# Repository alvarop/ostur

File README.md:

# Ostur - Cheese cave controller!

This is a work in progress for a cheese cave controller system.
The goal is to be able to control a mini fridge to get the right conditions for cheesemaking.

The project consists of:

* [Hardware](hw/) - A microcontroller and various temperature/humidity sensors
* [Firmware](fw/2.0/) - Code in the microcontroller to control the fridge and measure temperature/humidity values
* [Software](sw/2.0/) - Python scripts to communicate with the microcontroller to log and plot data

So far, it's been used to [make Brie](https://imgur.com/a/cGHID) [successfully](https://imgur.com/B5qB1kU)!

Once it's more user friendly, I'll add usage instructions so others can reproduce the setup.

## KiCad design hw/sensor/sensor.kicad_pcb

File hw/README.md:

# Ostur Hardware

To make some brie, there are 3 main components required:
1. An [Ostur controller](controller/) PCB
2. A controllable power outlet relay module. I'm using [this one](https://www.adafruit.com/product/2935) from Adafruit
3. 2+ [Ostur temperature/humidity sensors](humidity/). One for the fridge temperature and the rest for each aging container (if any).

Optional components are:
1. [Silicon Labs BLED112](https://www.digikey.com/products/en?keywords=1446-1030-ND) USB dongle for receiving BLE beacon data of the temperature/humidity.

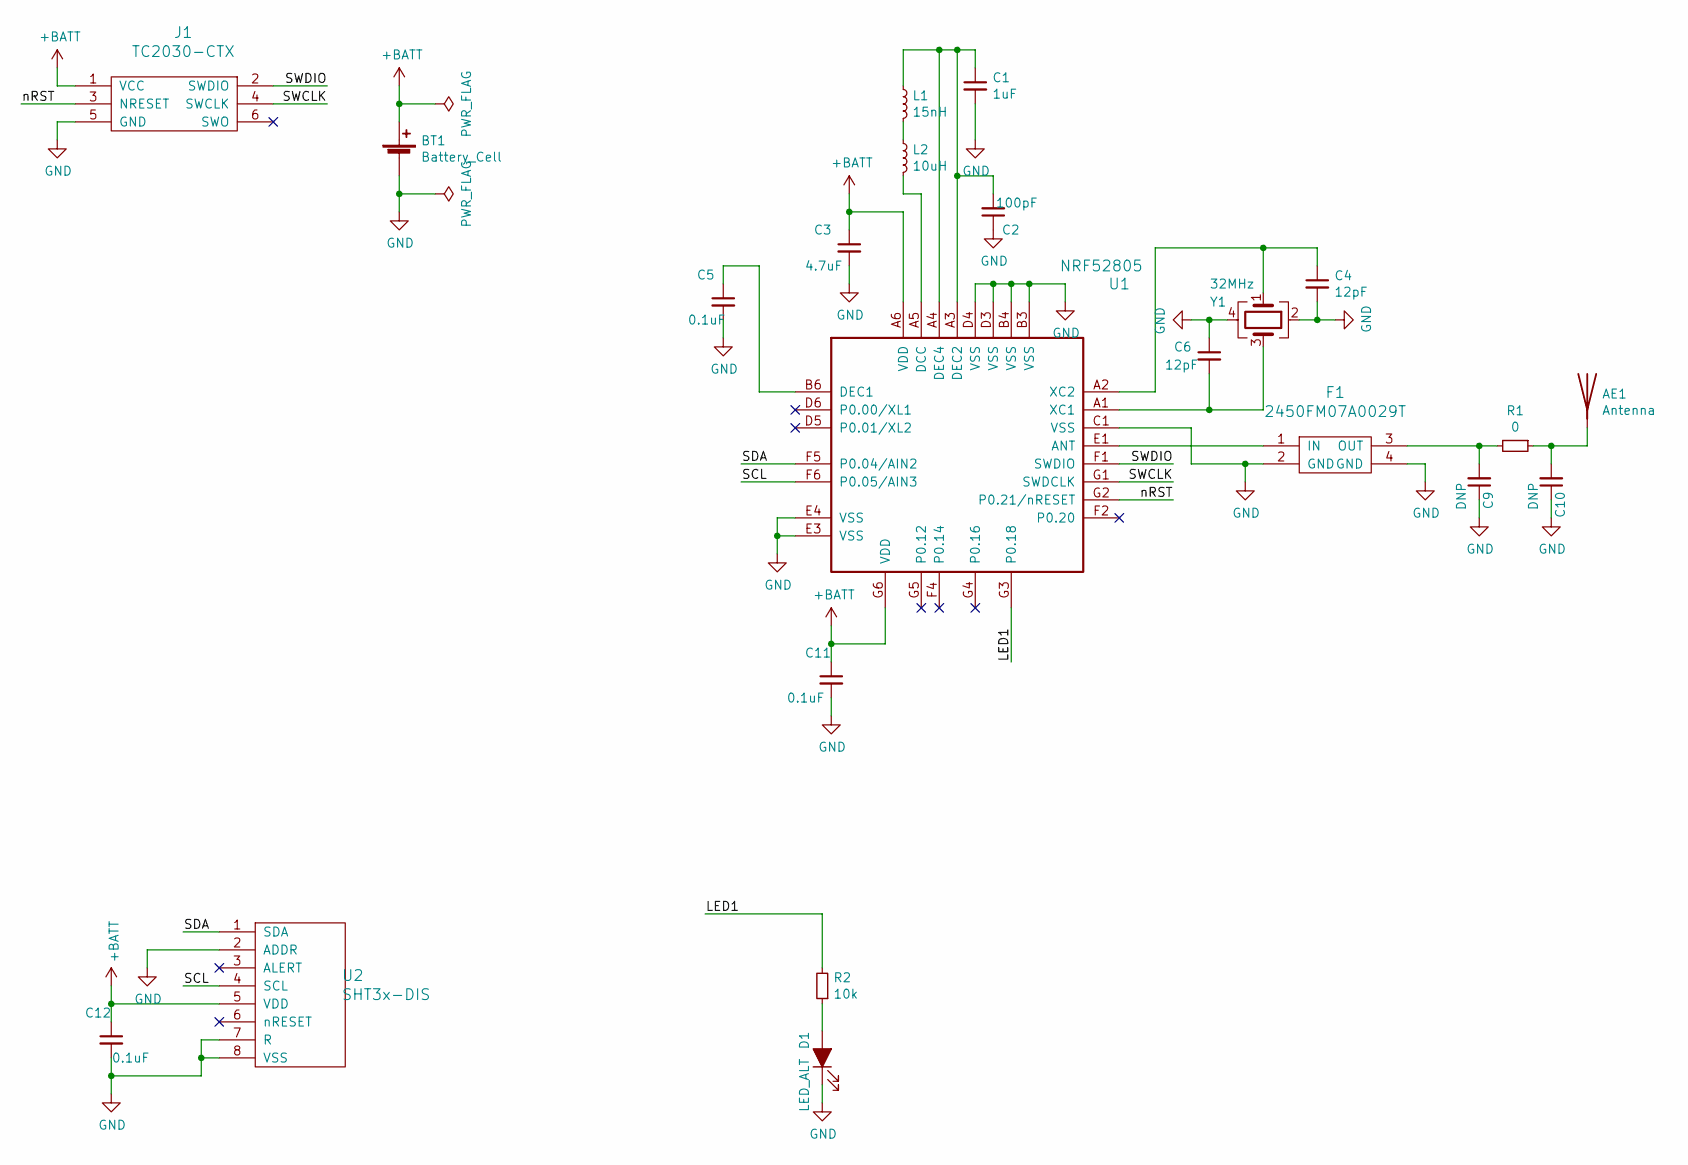
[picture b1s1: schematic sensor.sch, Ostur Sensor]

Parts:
AE1: Antenna; AMCA31-2R450G-S1F-T3; MPN AMCA31-2R450G-S1F-T3
BT1: Battery_Cell; BAT-HLD-001-THM; MPN BATT-HLD-001-THM
C1: 1uF; C_0402_1005Metric; MPN CC0402KRX5R5BB105
C2: 100pF; C_0402_1005Metric; MPN UMK105CG101JV-F
C3: 4.7uF; C_0402_1005Metric; MPN GRM155R60J475ME47D
C4, C6: 12pF; C_0402_1005Metric; MPN C0402C120J5GACTU
C5, C11, C12: 0.1uF; C_0402_1005Metric; MPN GRM155R61A104KA01D
C9, C10: DNP; C_0402_1005Metric
D1: LED_ALT; LED_0402_1005Metric; MPN QBLP595-IG
F1: 2450FM07A0029T; MPN 2450FM07A0029T
J1: TC2030-CTX; TC2030-NL
L1: 15nH; L_0402_1005Metric; MPN HK100515NJ-T‎
L2: 10uH; L_0603_1608Metric; MPN ‎LQM18FN100M00D‎
R1: 0; R_0402_1005Metric; MPN RC1005J000CS
R2: 10k; R_0402_1005Metric; MPN RC0402JR-0710KL
U1: NRF52805; MPN NRF52805-CAAA-R
U2: SHT3x-DIS; SHT3x; MPN SHT30-DIS-P2.5KS
Y1: 32MHz; Crystal_SMD_2016-4Pin_2.0x1.6mm; MPN CX2016DB32000D0FLJCC

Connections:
+BATT: BT1.1 (+), C3.1, C11.1, C12.1, J1.1 (VCC), U1.A6 (VDD), U1.G6 (VDD), U2.5 (VDD)
/LED1: R2.2, U1.G3 (P0.18)
/SCL: U1.F6 (P0.05/AIN3), U2.4 (SCL)
/SDA: U1.F5 (P0.04/AIN2), U2.1 (SDA)
/SWCLK: J1.4 (SWCLK), U1.G1 (SWDCLK)
/SWDIO: J1.2 (SWDIO), U1.F1 (SWDIO)
/nRST: J1.3 (NRESET), U1.G2 (P0.21/nRESET)
GND: BT1.2 (-), C1.2, C2.1, C3.2, C4.2, C5.2, C6.1, C9.1, C10.1, C11.2, C12.2, D1.1 (K), F1.2 (GND), F1.4 (GND), J1.5 (GND), U1.B3 (VSS), U1.B4 (VSS), U1.C1 (VSS), U1.D3 (VSS), U1.D4 (VSS), U1.E3 (VSS), U1.E4 (VSS), U2.2 (ADDR), U2.7 (R), U2.8 (VSS), Y1.2, Y1.4
unnamed: AE1.1, C10.2, R1.1
unnamed: C1.1, C2.2, L1.1, U1.A3 (DEC2), U1.A4 (DEC4)
unnamed: C4.1, U1.A2 (XC2), Y1.1
unnamed: C5.1, U1.B6 (DEC1)
unnamed: C6.2, U1.A1 (XC1), Y1.3
unnamed: C9.2, F1.3 (OUT), R1.2
unnamed: D1.2 (A), R2.1
unnamed: F1.1 (IN), U1.E1 (ANT)
unnamed: L1.2, L2.1
unnamed: L2.2, U1.A5 (DCC)

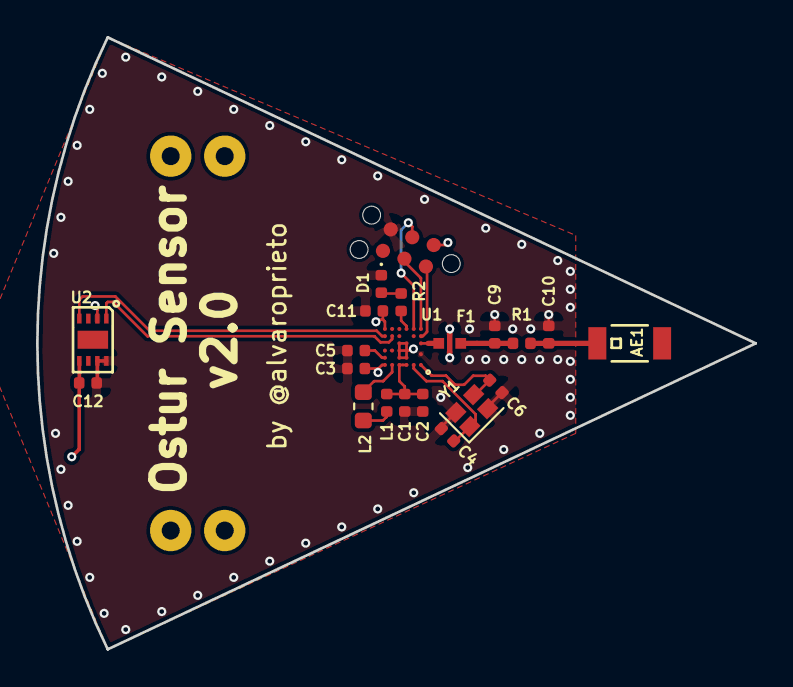
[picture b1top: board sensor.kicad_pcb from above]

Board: 4 copper layers, 39.9 x 34.0 mm, 22 parts (1 on the bottom side), 18 nets.

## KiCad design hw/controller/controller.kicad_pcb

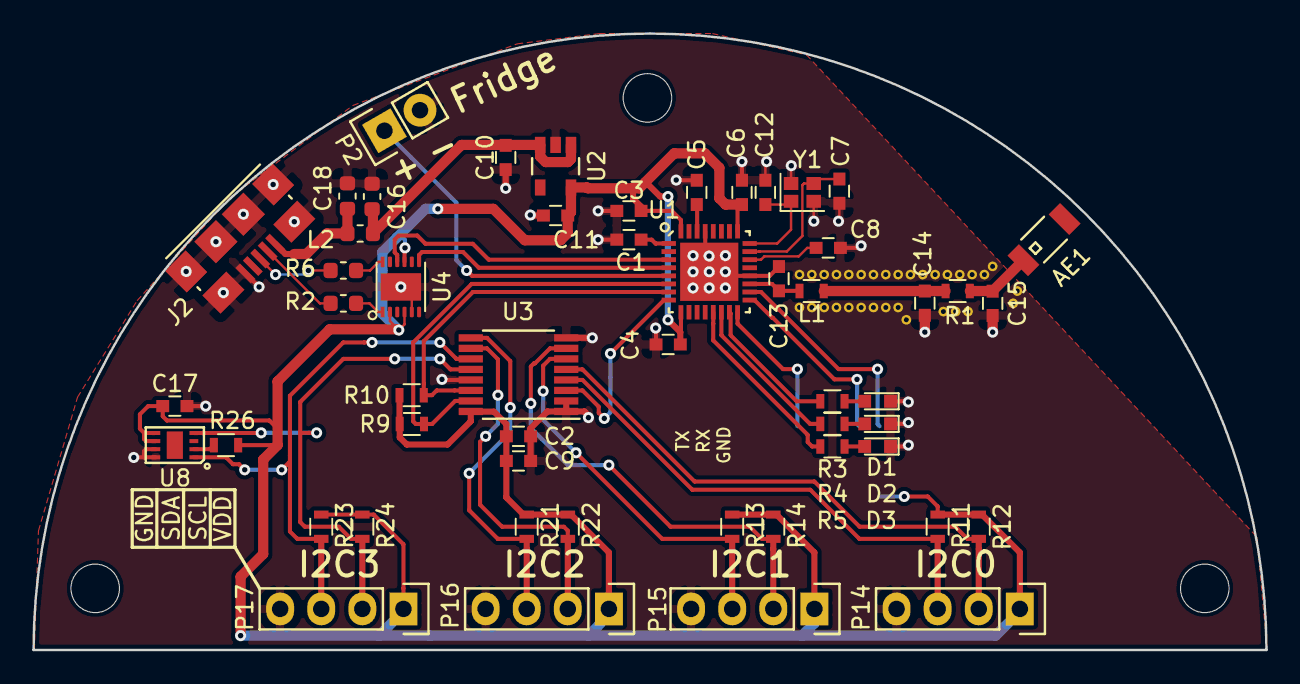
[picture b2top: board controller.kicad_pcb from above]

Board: 2 copper layers, 76.2 x 38.1 mm, 54 parts (1 on the bottom side), 40 nets.

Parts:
AE1: Antenna; AMCA31-2R450G-S1F-T3
C1, C4, C6, C17: 100nF; C_0603
C2: 10nF; C_0603
C3, C9: 4.7uF; C_0603
C5, C10, C11: 1uF; C_0603
C7, C12: 12pF; C_0603
C8: 100pF; C_0603
C13: 0.8pF; C_0603
C14, C15: DNP; C_0603
C16: 100nF; C_0603_1608Metric
C18: 10nF; C_0603_1608Metric
D1: LED0; LED_0603
D2: LED1; LED_0603
D3: LED2; LED_0603
J1: ARM-SWD; ARM_SWD_SMD
J2: USB_OTG; USB_MICRO_B
L1: 3.9nH; R_0603
L2: FB; R_0603_1608Metric
P2: FRIDGE; Pin_Header_Straight_1x02
P14: I2C0; Pin_Header_Straight_1x04
P15: I2C1; Pin_Header_Straight_1x04
P16: I2C2; Pin_Header_Straight_1x04
P17: I2C3; Pin_Header_Straight_1x04
R1: 0; R_0603
R2, R6: 27; R_0603_1608Metric
R3, R4, R5: 680; R_0603
R9, R10, R11, R12, R13, R14, R21, R22, R23, R24, R26: 10k; R_0603
U1: NRF52810-QCAA; NRF52810_QCAA_QFN32
U2: MIC550X; SOT-23(M5)
U3: tca9546a; TSSOP-16_4.4x5mm_Pitch0.65mm
U4: FT234XD; FTDI_DFN12
U8: SHT3x-DIS; SHT3x
Y1: 32MHz; Crystal_SMD_2016-4pin_2.0x1.6mm

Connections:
+5V: C10.1, C16.1, L2.2, U2.1, U2.3
/ADDR_LOCAL: R26.1, U8.2
/FRIDGE: P2.1, U1.5
/LED0: R3.2, U1.15
/LED1: R4.2, U1.14
/LED2: R5.2, U1.13
/SCL: R10.2, U1.7, U3.14
/SCL0: P14.2, R12.2, U3.5
/SCL1: P15.2, R14.2, U3.7
/SCL2: P16.2, R22.2, U3.10
/SCL3: P17.2, R24.2, U3.12, U8.4
/SDA: R9.2, U1.6, U3.15
/SDA0: P14.3, R11.2, U3.4
/SDA1: P15.3, R13.2, U3.6
/SDA2: P16.3, R21.2, U3.9
/SDA3: P17.3, R23.2, U3.11, U8.1
/SWDCLK: J1.4, U1.17
/SWDIO: J1.2, U1.18
/TCA_nRST: U1.8, U3.3
/UART1_RX: U1.4, U4.7
/UART1_TX: U1.3, U4.10
/USB_DM: J2.2, R2.1
/USB_DP: J2.3, R6.2
/VDD_5: C18.1, J2.1, L2.1
/nRST: J1.10, U1.16
GND: C1.2, C2.2, C3.2, C4.2, C5.2, C6.2, C7.2, C8.1, C9.2, C10.2, C11.2, C12.1, C13.1, C14.1, C15.1, C16.2, C17.2, C18.2, D1.1, D2.1, D3.1, J1.3, J1.5, J2.5, J2.6, P2.2, P14.4, P15.4, P16.4, P17.4, U1.20, U1.29, U2.2, U3.1, U3.2, U3.8, U3.13, U4.5, U8.7, U8.8, Y1.2, Y1.4
unnamed: AE1.1, C15.2, R1.2
unnamed: C1.1, U1.1
unnamed: C5.1, U1.30
unnamed: C7.1, U1.23, Y1.3
unnamed: C8.2, U1.22
unnamed: C12.2, U1.24, Y1.1
unnamed: C13.2, L1.1, U1.19
unnamed: C14.2, L1.2, R1.1
unnamed: D1.2, R3.1
unnamed: D2.2, R4.1
unnamed: D3.2, R5.1
unnamed: R2.2, U4.1
unnamed: R6.1, U4.12
VDD: C2.1, C3.1, C4.1, C6.1, C9.1, C11.1, C17.1, J1.1, P14.1, P15.1, P16.1, P17.1, R9.1, R10.1, R11.1, R12.1, R13.1, R14.1, R21.1, R22.1, R23.1, R24.1, R26.2, U1.9, U1.25, U1.32, U2.5, U3.16, U4.2, U4.4, U4.9, U8.5, U8.6

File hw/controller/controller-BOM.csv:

Title,Ostur Controller
Revision,2.0
Date,2018-01-22
Generated,Fri 02 Feb 2018 03:28:43 AM PST
Company,alvarop.com
Comment 1,
Comment 2,
Comment 3,
Comment 4,
Total Parts,49
Total Unique Parts,29



Ref,Qty,Value,Footprint,MPN,
AE1 ,1,Antenna,alvarop:AMCA31-2R450G-S1F-T3, 
C10 C11 C5 ,3,1uF,Capacitors_SMD:C_0603,CL21F105ZAFNNNG
C2 ,1,10nF,Capacitors_SMD:C_0603,CL21B103KBANNNC
C17 C4 C6 C1 ,4,100nF,Capacitors_SMD:C_0603,CL21B104MBCNNNC
C9 C3 ,2,4.7uF,Capacitors_SMD:C_0603,CL21A475KQFNNNG
C12 C7 ,2,12pF,Capacitors_SMD:C_0603, 
C8 ,1,100pF,Capacitors_SMD:C_0603, 
C13 ,1,0.8pF,Capacitors_SMD:C_0603, 
C14 C15 ,2,DNP,Capacitors_SMD:C_0603, 
D3 ,1,LED2,LEDs:LED_0603,LG R971-KN-1
D2 ,1,LED1,LEDs:LED_0603,LG R971-KN-1
D1 ,1,LED0,LEDs:LED_0603,LG R971-KN-1
J2 ,1,USB_OTG,footprints:USB_MICRO_B,10118192-0001LF
J3 ,1,UART,Pin_Headers:Pin_Header_Straight_1x03_Pitch1.27mm, 
J1 ,1,ARM-SWD,alvarop:ARM_SWD_SMD, 
L1 ,1,3.9nH,Resistors_SMD:R_0603, 
P14 ,1,I2C0,Pin_Headers:Pin_Header_Straight_1x04_Pitch2.54mm, 
P15 ,1,I2C1,Pin_Headers:Pin_Header_Straight_1x04_Pitch2.54mm, 
P16 ,1,I2C2,Pin_Headers:Pin_Header_Straight_1x04_Pitch2.54mm, 
P17 ,1,I2C3,Pin_Headers:Pin_Header_Straight_1x04_Pitch2.54mm, 
P2 ,1,FRIDGE,Pin_Headers:Pin_Header_Straight_1x02_Pitch2.54mm, 
R5 R4 R3 ,3,680,Resistors_SMD:R_0603,RC0805JR-07680RL
R11 R12 R9 R10 R13 R14 R21 R22 R23 R24 R26 ,11,10k,Resistors_SMD:R_0603,311-10KARCT-ND
R1 ,1,0,Resistors_SMD:R_0603, 
U3 ,1,tca9546a,Housings_SSOP:TSSOP-16_4.4x5mm_Pitch0.65mm,TCA9546APWR
U2 ,1,MIC550X,footprints:SOT-23(M5), 
U8 ,1,SHT3x-DIS,footprints:SHT3x, 
U1 ,1,NRF52810-QCAA,alvarop:NRF52810_QCAA_QFN32, 
Y1 ,1,32MHz,Crystals:Crystal_SMD_2016-4pin_2.0x1.6mm,CX2016DB32000D0FLJCC




BOM made with KICAD_BOM_WIZARD (https://github.com/HashDefineElectronics/KiCad_BOM_Wizard.git)
Generated Fri 02 Feb 2018 03:28:43 AM PST

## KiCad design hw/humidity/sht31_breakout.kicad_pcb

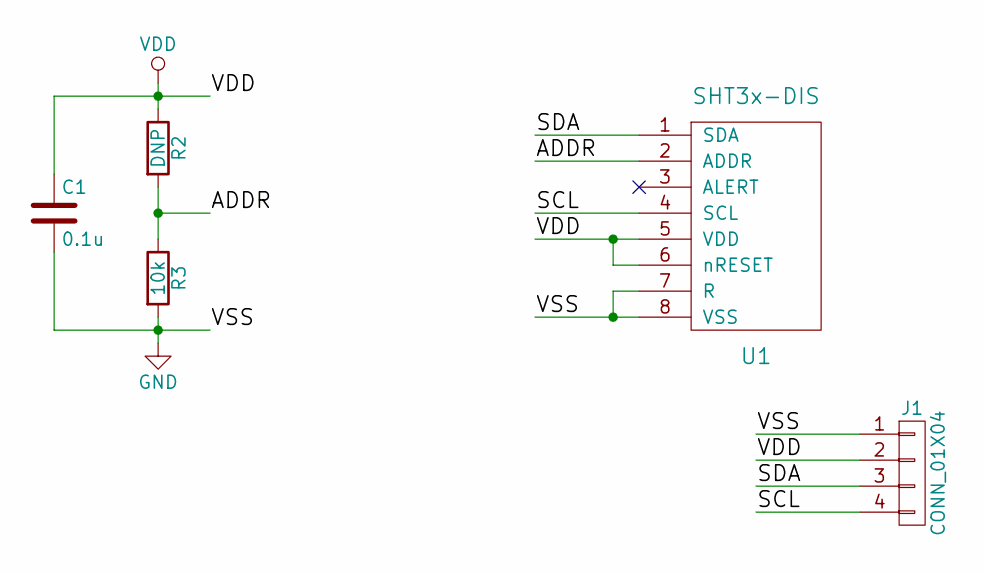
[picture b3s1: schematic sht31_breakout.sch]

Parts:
C1: 0.1u; C_0603
J1: CONN_01X04; Pin_Header_Straight_1x04_Pitch2.54mm
R2: DNP; C_0603
R3: 10k; C_0603
U1: SHT3x-DIS; SHT3x

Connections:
/ADDR: R2.2, R3.1, U1.2 (ADDR)
/SCL: J1.4, U1.4 (SCL)
/SDA: J1.3, U1.1 (SDA)
GND: C1.2, J1.1, R3.2, U1.7 (R), U1.8 (VSS)
VDD: C1.1, J1.2, R2.1, U1.5 (VDD), U1.6 (nRESET)

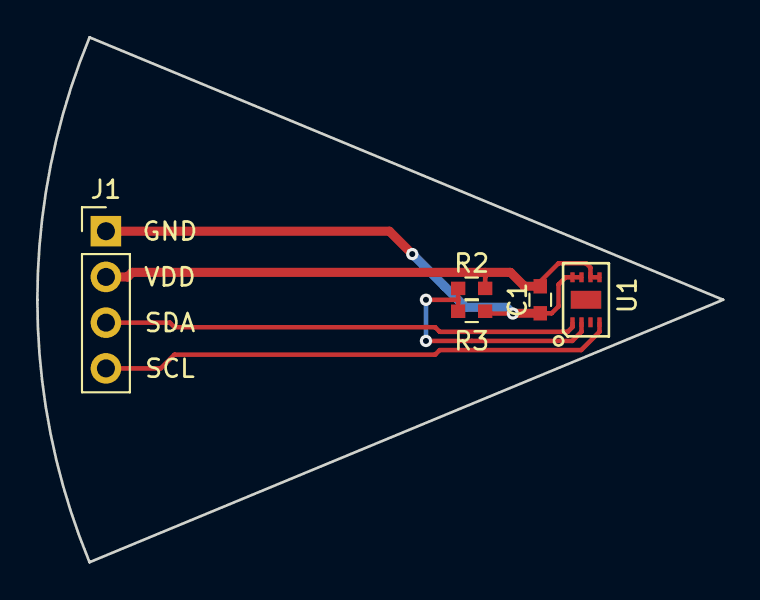
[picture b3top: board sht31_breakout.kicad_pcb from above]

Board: 2 copper layers, 38.1 x 29.2 mm, 5 parts (0 on the bottom side), 5 nets.

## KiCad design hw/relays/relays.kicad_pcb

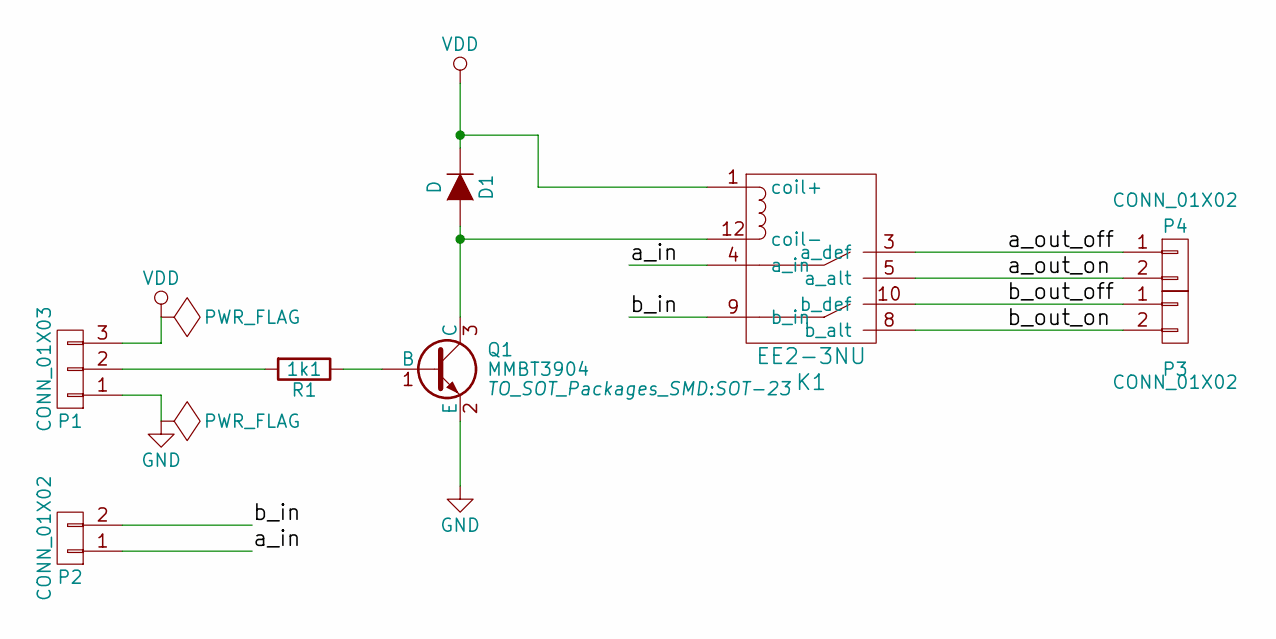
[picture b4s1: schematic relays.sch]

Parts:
D1: D; SOD-80; MPN LL4148
K1: EE2-3NU; MPN EE2-3NU-L
P1: CONN_01X03; Pin_Header_Straight_1x03
P2, P3, P4: CONN_01X02; Pin_Header_Straight_1x02
Q1: MMBT3904; SOT-23; MPN MMBT3904,215
R1: 1k1; R_0805; MPN RMCF0805JT1K00

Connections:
/a_in: K1.4 (a_in), P2.1
/a_out_off: K1.3 (a_def), P4.1
/a_out_on: K1.5 (a_alt), P4.2
/b_in: K1.9 (b_in), P2.2
/b_out_off: K1.10 (b_def), P3.1
/b_out_on: K1.8 (b_alt), P3.2
GND: P1.1, Q1.2 (E)
unnamed: D1.2 (A), K1.12 (coil-), Q1.3 (C)
unnamed: P1.2, R1.2
unnamed: Q1.1 (B), R1.1
VDD: D1.1 (K), K1.1 (coil+), P1.3

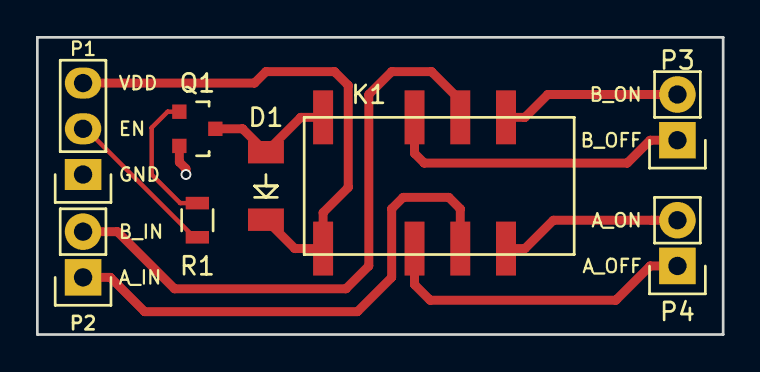
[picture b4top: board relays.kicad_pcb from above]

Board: 2 copper layers, 38.1 x 16.5 mm, 8 parts (0 on the bottom side), 11 nets.

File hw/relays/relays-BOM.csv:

Title,
Revision,
Date,
Generated,Fri 20 Jan 2017 06:25:38 PM PST
Company,
Comment 1,
Comment 2,
Comment 3,
Comment 4,
Total Parts,8
Total Unique Parts,6



Ref,Qty,Value,Footprint,MPN,
D1 ,1,D,footprints:SOD-80,LL4148
K1 ,1,EE2-3NU,footprints:EE2-3NU,EE2-3NU-L
P1 ,1,CONN_01X03,Pin_Headers:Pin_Header_Straight_1x03, 
P2 P3 P4 ,3,CONN_01X02,Pin_Headers:Pin_Header_Straight_1x02, 
Q1 ,1,MMBT3904,TO_SOT_Packages_SMD:SOT-23,MMBT3904 215
R1 ,1,1k1,Resistors_SMD:R_0805,RMCF0805JT1K00




BOM made with KICAD_BOM_WIZARD (https://github.com/HashDefineElectronics/KiCad_BOM_Wizard.git)
Generated Fri 20 Jan 2017 06:25:38 PM PST

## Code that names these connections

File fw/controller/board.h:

#ifndef __BOARD_H__
#define __BOARD_H__

#include "stm32f0xx.h"

#define LED0_PORT GPIOB
#define LED0_PIN 0

#define LED1_PORT GPIOB
#define LED1_PIN 1

#define LED2_PORT GPIOB
#define LED2_PIN 2

#define UART1_TX_PORT GPIOA
#define UART1_TX_PIN 9

#define UART1_RX_PORT GPIOA
#define UART1_RX_PIN 10

#define SDA_PORT GPIOB
#define SDA_PIN 7

#define SCL_PORT GPIOB
#define SCL_PIN 6

#define TCA_nRST_PORT GPIOB
#define TCA_nRST_PIN 8

#define MIST_PORT GPIOA
#define MIST_PIN 3

#define PUMP_PORT GPIOA
#define PUMP_PIN 4

#define FAN_PORT GPIOA
#define FAN_PIN 5

#define FRIDGE_PORT GPIOA
#define FRIDGE_PIN 6

#endif  // __BOARD__

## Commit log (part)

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2016-09-29 First working AM2315 code
2016-09-29 Adding additional (analog) temperature sensors for inside/outside temp comparison
2016-10-01 Split ostur into separate file
2016-10-01 Start organizing files and added experimental web based control server
2016-10-05 Make standard interface for relay control
2016-10-05 Adding test logger script that requests data from the control_server over http and saves it to an sqlite db
2016-10-05 Adding script to plot temp/humidity from a sqlite db
2016-10-09 Don't look at db files
2016-10-09 Start using the sqlite .execute() args to make sure the data is escaped for the query (just in case)
2016-10-09 Adding relay_status() to Ostur and exposing it via /relays on the control server
2016-10-20 Minor limit update
2016-10-26 Silly way of changing filename case in OS X (Part 1)
2016-10-26 Silly way of changing filename case in OS X (Part 2)
2016-10-29 Update for name change
2016-10-29 Start using i2c mux for experiment
2016-10-29 Adding si7021 support
2016-10-29 Adding htu21d support
2016-10-29 Adding sht31 support
2016-11-02 Adding ostur_controller
2016-11-02 Add thlogger and thplotter
2016-11-02 Adding some misc files
2016-11-14 Start work on controller prototype
2016-11-15 Placement mostly done and half routed
2016-11-16 Passing DRC!
2016-11-16 Ostur Controller Layout 1.0 done!
    I think...
2016-11-28 Fixed GPIO label and moved resistor
2016-11-29 Updated part numbers for controller
2016-12-10 Initial commit of controller firmware. Basic console
2016-12-10 Make sure fw release string is accurate
2016-12-10 Split uart functionality to separate file
2016-12-10 Start using board file and removing trailing spaces...
2016-12-10 Start adding I2C. Tx seems to be working
2016-12-10 Adding todo for hw controller
2017-01-04 adding timer.c/h
2017-01-04 adding tca9584 driver
2017-01-04 adding sht31 driver
2017-01-04 Adding SHT console command
    NOTE: i2c is not stable yet. Stops working whenever a bad read happens.
    Need to debug...
2017-01-05 Add fix for i2c reads after NACK
    The transmit data register isn't cleared when a NACK occurs on
    the previous transaction. This manually flushes the register
    so the next one will work.
2017-01-05 Actually check the correct register value
2017-01-06 Start adding config.c/h (not yet working)
2017-01-06 Increasing UART FIFO to 2048 for now
2017-01-06 Config seems to be writing to flash :D
2017-01-06 Remove old LED debug stuff
2017-01-06 Update default configuration
2017-01-06 adding sht31_init function
2017-01-06 Adding initial controller code (just prints values at interval)
2017-01-10 Adding simple relay board
2017-01-10 Adding ARM SWD connector to kicad lib
2017-01-12 Updated ostur controller to v1.1
    Some changes:
    Reduced i2c to 4 channels instead of 8
    Added ARM-SWD 10-pin connector
    Removed 8MHz crystal (not needed for usb)
    Added actual footprint for 32.768kHz crystal
    Moved uart, not sure why though...
2017-01-18 Updating part numbers for ostur controller
2017-01-18 updating TODO
2017-01-18 Adding sheet details for ostur controller
2017-01-18 Adding ostur controller BOM
2017-01-18 Updating cmdBuff to 1024 bytes instead of 64
2017-01-18 Updating sht31 reset delay and address bug
2017-01-18 Adding controller autoconfig command to auto-discover sht31 sensors
2017-01-18 Adding config fields for primary and outside sensors
2017-01-18 Update controller to sample all sensors, then print
2017-01-18 Initialize relay control GPIOs
2017-01-18 Update sample rate to 2s and temp setting to 10C
2017-01-18 Start controllng!
2017-01-19 Update ostur controller firmware output and printout
2017-01-19 Adding quick script to merge db files
2017-01-19 Start using debug prints :D
2017-01-21 Adding part numbers for relays board
2017-01-24 Adding flags (and autostart)
2017-01-24 Adding controller stopped acknowledgement
2017-01-24 Increasing averaging buffer size
2017-01-24 Update Ostur.py to work with ostur controller fw (not silta)
2017-01-25 Adding minimum off time for fridge
    To protect the compressor from short cycling
2017-01-26 Make sure SystemCoreClock() is correct even without 8MHz xtal
2017-01-26 Start using HSI48 instead of HSE
2017-01-26 Change default config to 5 second period
2017-01-26 Update ostur.py so it doesn't time out so quick qaiting for sample
2017-01-27 Enable device RTC for real time and dates!
2017-01-27 Start saving real time when logging!
2017-01-27 Reverting to old timestamp until RTC drift is reduced
2017-01-27 Updating sweet db merge tool
2017-01-27 Try to recover from i2c errors in fw
2017-01-27 Don't crash when errors happen, just print them out...
2017-01-29 Fixed EE2-3NU Footprint
2017-01-29 Fix relay board after bad footprint fix
2017-01-29 Adding get_time function
2017-01-29 Change main config to RAM (loads from flash at boot)
2017-01-31 Make tca driver more generic (for 4/8 ch parts)
2017-01-31 Switch to 4 channel part
2017-01-31 Adding heater enable/disable for SHT31D
2017-02-02 Made much smaller SHT31 breakout
    We'll see if I can hand solder it...
2017-02-04 RTC crystal update for schematic and BOM
2017-02-04 Finally got RTC working :D
2017-02-04 Adding flags config option
2017-02-04 Lowered drive current for LSE
2017-02-04 Adding via footprint for stitched pours
2017-02-04 Updating ostur controller!
    Removed unused headers
    Added extra shielding for 32768Hz crystal
    Made board smaller
2017-02-05 Improve plotter with actual dates and legends!
2017-02-05 Cleaning up python drivers
    (Moving to silta repo)
2017-02-05 Getting rid of old files, moving some current ones around
2017-02-12 Adding a bunch of footprints
2017-02-12 Fixed silkscreen on parts
2017-02-15 Add averaging window to ostur_plot_db.py
    Multi-week plots were starting to make python struggle
2017-02-19 Updating to newer kicad version
2017-02-19 Adding labels for LSE in/out pins
2017-03-11 Fixed controller PCB...
    Somehow I forgot to connect some VDD lines on the micocontroller.....
2017-03-11 something something kicad update....
2017-03-11 Update pins for newest version
2017-03-29 Fix i2c driver
2017-03-29 Updating readme
2017-04-01 Enable all the clocks
2017-07-15 I2C Fix & #define Fix
2017-07-15 Start designing flex pcb :D
2017-07-18 Added silkscreen and stiffener
2017-08-19 Adding cheese wedges!
2017-08-19 Placement mostly done
2017-08-19 Layout done for Ostur Controller v1.3
2017-08-20 Cleaning up Ostur.py
    Removed old dependencies/comments
2017-08-21 Added USB CDC support for Ostur Controller
    No more USB-Serial adapters needed!
2017-08-21 Disabled echo and another usb not ready fix
2017-08-21 adding debug stuff for ostur_log.py
2017-08-23 Catch Overflow errors during debug
2017-08-24 Fixing bug in USB code that was eating my bytes
    At least I think I fixed it...
2017-09-04 Plot more channels!
2017-09-09 Updating BOM for latest controller version
2017-09-09 Add TCA95xx hard reset when unable to communicate
2017-09-10 Exit script on error for debugging
    Having signal integrity issues with Raspberry Pi near the fridge. The usb connection sometimes drops.
    Exiting the script for now. (I have a shell script that re-starts with alternating file descriptors for now)
2017-09-13 Trying to get more consistent looking code
    Applied `clang-format -style=Google <filename>` to the files I created
2017-09-13 Updating fifo function names
2017-09-13 Updating SHT function names
2017-09-13 Updating TCA95xxa filenames
2017-09-14 Updating Timer function names
2017-09-14 Updating UART function names
2017-09-14 Updating Controller function names
2017-09-14 Updating console function names
2017-09-14 Updating config function names
2017-09-14 Make sure build dir is auto-created
2017-09-14 PEP8!
2017-09-15 Enabling DFU over usb console!
    No more pushing dfu button :)
2017-09-16 Fix misspelling
2017-10-04 Updated sht31 breakout to be wedge shaped!
2017-10-04 Removed sensor breakouts from controller
    Updated silkscreen
    Removed SWD connector
2017-11-19 Fixed silkscreens on controller/sensor
    And submitted to pcbcart!
2017-11-26 Fix printing of negative floats
2017-11-26 Fix controller bugs
    Could only read from default sensor address, even when autodetecting the alternate.
    Added TCA95xx workaround for all cases
2017-11-26 Update default configuration for latest hardware
2018-01-22 Updated ostur_controller with NRF52810. Released v2.0
2018-02-02 Updating BOM and silkscreen fixes for controller 2.0
2018-02-02 Moving old fw to 1.0 directory
2018-02-04 First (semi-)working mynewt project
    For some reason it only works with a debugger attached :'(
2018-02-04 Start using the OS properly
2018-02-04 Adding console printing
2018-02-04 Got basic BLE working!
2018-02-04 No more blinky
2018-02-04 Adding i2c, txa95xxa, and sht3x drivers
    I2C fails hard when a device NACK's though...
2018-02-04 Finally got SHT3X working :D
2018-02-04 Re-structuring directories
2018-02-04 Adding pipfile
2018-02-04 Adding bglib
2018-02-25 Temporarily adding nrf52810dk bsp
2018-02-25 Minor fixes to work with latest mynewt-core
2018-02-26 updating hal_bsp.c
2018-02-28 Adding fridge control
2018-03-03 Ostur FW 2.0 seems to be working!
    FW autodetects up to 8 SHT3x temp/humidity sensors and requires
    a minimum of 2 to run the fridge (one inside and one outside).
    Device beacons out each sensor temperature/humidity over BLE periodically
2018-03-03 Adding ble receiver and plotting scripts
    To run, use pipenv run sw/2.0/scripts/simple_scan.py ...
2018-03-11 Adding sqlite support to simple_scan.py
2018-03-11 Adding simple flask ostur_viewer
2018-03-11 Adding csv_to_sqlite.py
2018-03-13 Updating documentation
2018-03-13 Fixing readme urls
2018-03-14 More readme updates!
2018-07-20 Released Ostur Controller v2.1
    NOTE: Used kicad 5
2018-08-04 Updating to newt version 1.4.1 and apache newt repo
2018-08-09 Add hourly average to display
2018-08-20 Adding last door opened time
2018-08-21 Adding db commit retries
    Having trouble while running with ostur_viewer in a raspberry pi
    zero
2019-06-29 Started working on ostur sensor
2019-07-02 Finished ostur sensor and released to oshpark
2019-10-06 Update mynewt libraries
2019-10-06 Switch sht3x library to use simple_adc driver
2019-10-06 Add ostur sensor v1.0 BSP and app
2019-10-06 add script to monitor new ostur sensors
2019-10-06 Adding nrf52811_usb fw
2019-10-06 Adding ostur_usb_scanner.py and supporting scripts
2019-10-06 Get rid of magic number in packet and move it to mfg_data
2019-10-06 Adding OsturDB (ported from ChaacDB)
2019-10-06 Adding ostur_frontend scripts!
2019-10-07 fixed setup path
2019-10-07 moving ostur_usb_scanner to ostur_logger
2019-10-07 forgot to change this
2019-10-07 remove some chaacs and return port to 80
2019-10-07 one more config fix
2019-10-11 Released Ostur Sensor v1.1 to JLCPCB
    Changes:
    * Changed to 4 layer board for better RF performance
    * Changed RF trace to match 50Ohms on JLCPCB's JLC7628 stackup
    * Added decoupling capacitor for SHT3x
    * Changed I2C pull-ups to 0402's
    * Fixed silkscreen issues
2019-11-01 Fix ostur_frontend
2019-11-01 fixed de-duplication code
2019-12-01 Add ability to rename device (and sanitize user input!)
2019-12-01 Add ability to list devices as well as renaming
2019-12-01 Use safer sql queries
2019-12-01 no pipenv on rpi
2019-12-02 show device names instead of uid's if available
2020-02-09 Stop using LFXO and start using LFRC
    Power consumption goes up from ~1uA idle to ~1.5-1.6uA
2020-07-10 Update to use latest mynewt
2020-07-10 fix possibly unaligned pointer code
2020-07-10 Ignore virtualenvs
2020-07-12 Always use LP clock for CPU time (bootloader especially)
2021-01-02 Not sure why I never committed this.
    Using NRF52805
2021-01-03 Trying out influxdb
2022-01-15 Make a few changes to make this compile in 2022
2022-01-15 Create ostur pip package
    Update readme and added requirements.txt for ostur_logger
